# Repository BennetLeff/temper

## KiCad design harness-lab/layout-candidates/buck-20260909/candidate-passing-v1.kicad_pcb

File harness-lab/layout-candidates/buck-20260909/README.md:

# Buck layout candidate — 2026-09-09

`candidate.kicad_pcb` is the verified v4 regrouping of the protected
`buck-dev-a` fixture. Open it directly in KiCad. `compact_candidate.py`
reproduces the placement and routing from `candidate-passing-v1.kicad_pcb`
through KiCad 10.0.4's native API. It resets to that checkpoint on each run;
new track UUIDs mean regenerated bytes need fresh measurements.

The controller sits between the input capacitor above it and the bootstrap
capacitor below it. The feedback divider is on its quiet left side. The
inductor and three output capacitors form a power path to the right. All
nine functional components were placed explicitly; the three terminal
proxies, 50 × 40 mm outline, footprint pad geometry, nets, and rules retain
their frozen identities. No production PCB was edited.

## Verified measurements

| Check | v4 result |
|---|---:|
| Native DRC, including warnings | 0 violations |
| Unconnected items | 0 |
| C9 input pad → U3 VIN copper path | 5.4375 mm |
| C9 ground pad → U3 GND copper path | 11.2875 mm |
| Narrowest power track | 0.6 mm |
| Native reference labels | 12, all 1.0 mm high |
| Electrical/presentation layout judges | pass/pass |
| Atopile-to-PCB circuit integrity | pass |

Board SHA-256:
`03d26c713a13ce1385b49d5582539b27722303341e01de435b9233be5d0e3ee1`.
Protected semantic SHA-256 remains
`e07cf8a38c9066662c222a56ab5304ab0b2659b5b3230561f6c21e3efbc8d2d6`.
`drc.json`, `native-measure.json`, `v4-layout-result.json`, and
`engineering-evidence/` retain the native and Rust results. The full run is
`harness-lab/runs/engineering-audit2-compact-v4/`.

The earlier witness had a 43.7 mm ground route. V1's shortcut achieved
4.489171 mm while retaining the old placement. V4 trades a longer 11.2875 mm
ground route for clearer grouping and a shorter input route. Both meet this
experiment's 20 mm path limit; that limit is a harness proxy, not a TI
electrical specification or proof of acceptable EMI.

## Physical coverage limitation

L2's copied footprint explicitly says **"Stub for Bourns SRP1265A
inductor."** It has two pads, no courtyard, and no 3D body. The native render
therefore shows bare pads, not an inductor envelope. DRC cannot detect body
collisions for this footprint, and the footprint's land pattern is not
manufacturing-qualified.

The Bourns drawing specifies a 13.5 ±0.5 by 12.5 ±0.3 mm body. V4 reserves
the maximum 14.0 × 12.8 mm rectangle around L2, shown on `User.Drawings`;
other components sit outside it. This is a mechanical review aid, not a new
DRC rule or exact 3D model. The terminal footprints are also fixture proxies.
An actual board needs a verified land pattern, courtyard, connectors, and
appropriate copper/thermal design before fabrication. The copied frozen
project continues to ignore `missing_courtyard`; no rule was relaxed here.

The circuit-identity and local layout checks pass. Component derating, model qualification,
16 unresolved mandatory requirements, and powered hardware evidence remain
separate gates. `engineering-evidence/report.json` correctly reports the
complete reference as ineligible.

## Retained attempts

- V1: passing checkpoint, old placement and ground shortcut; its native
  measurements/render are explicitly named `*-v1`.
- V2: 26 DRC violations and 12 opens, retained as `candidate-v2-failed`.
- V3: 23 DRC violations and 2 opens, retained as `candidate-v3-failed`.
- V4 initial check: routing connected and clear; two U3 silkscreen overlaps
  in `v4b-check` were fixed by moving its reference.
- V4 label collection exposed KiCad's required `GetShownText(False)`
  argument. The collector and native visible-label regression now cover it.

The qualitative layout guidance comes from [TI LMR51430 section 9.4](https://www.ti.com/lit/ds/symlink/lmr51430.pdf).
The body envelope comes from the [Bourns SRP1265A drawing](https://bourns.com/docs/product-datasheets/srp1265a.pdf).

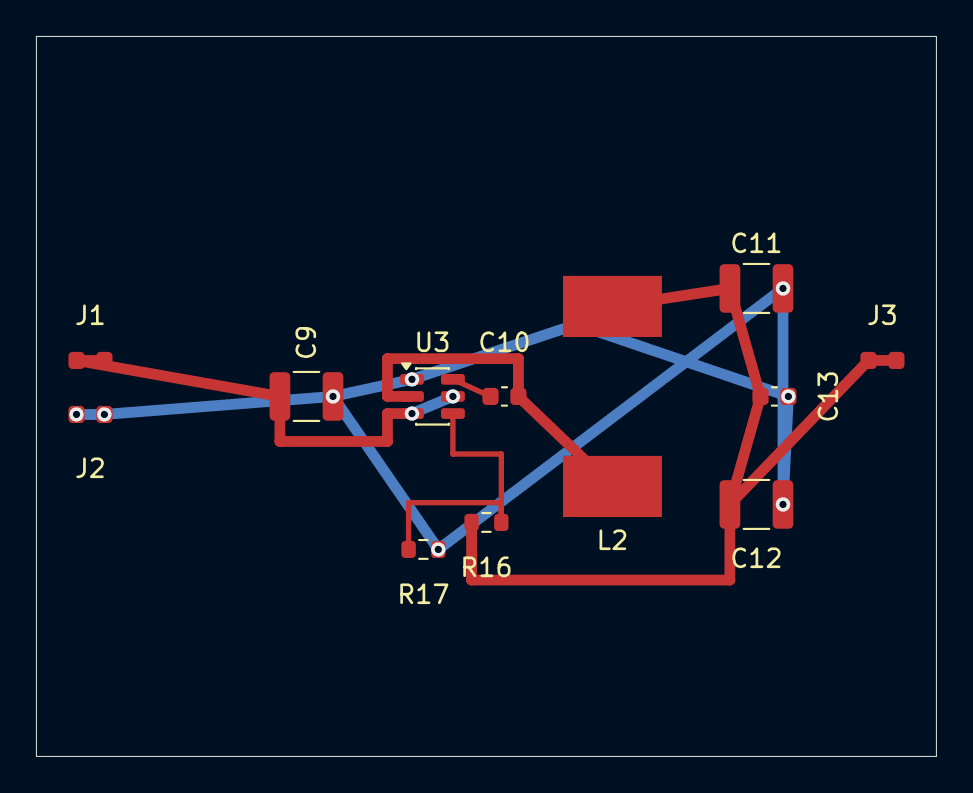
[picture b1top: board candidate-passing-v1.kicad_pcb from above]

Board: 2 copper layers, 50.0 x 40.0 mm, 12 parts (0 on the bottom side), 6 nets.

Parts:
C9: ?; C9
C10: ?; C10
C11: ?; C11
C12: ?; C12
C13: ?; C13
J1: J1
J2: J2
J3: J3
L2: ?; L2
R16: ?; R16
R17: ?; R17
U3: ?; U3

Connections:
+3V3: C11.1, C12.1, C13.1, J3.1, J3.2, L2.2, R16.1
+15V: C9.1, J1.1, J1.2, U3.3, U3.5
boot: C10.1, U3.6
fb: R16.2, R17.1, U3.4
gnd: C9.2, C11.2, C12.2, C13.2, J2.1, J2.2, R17.2, U3.1
sw: C10.2, L2.1, U3.2

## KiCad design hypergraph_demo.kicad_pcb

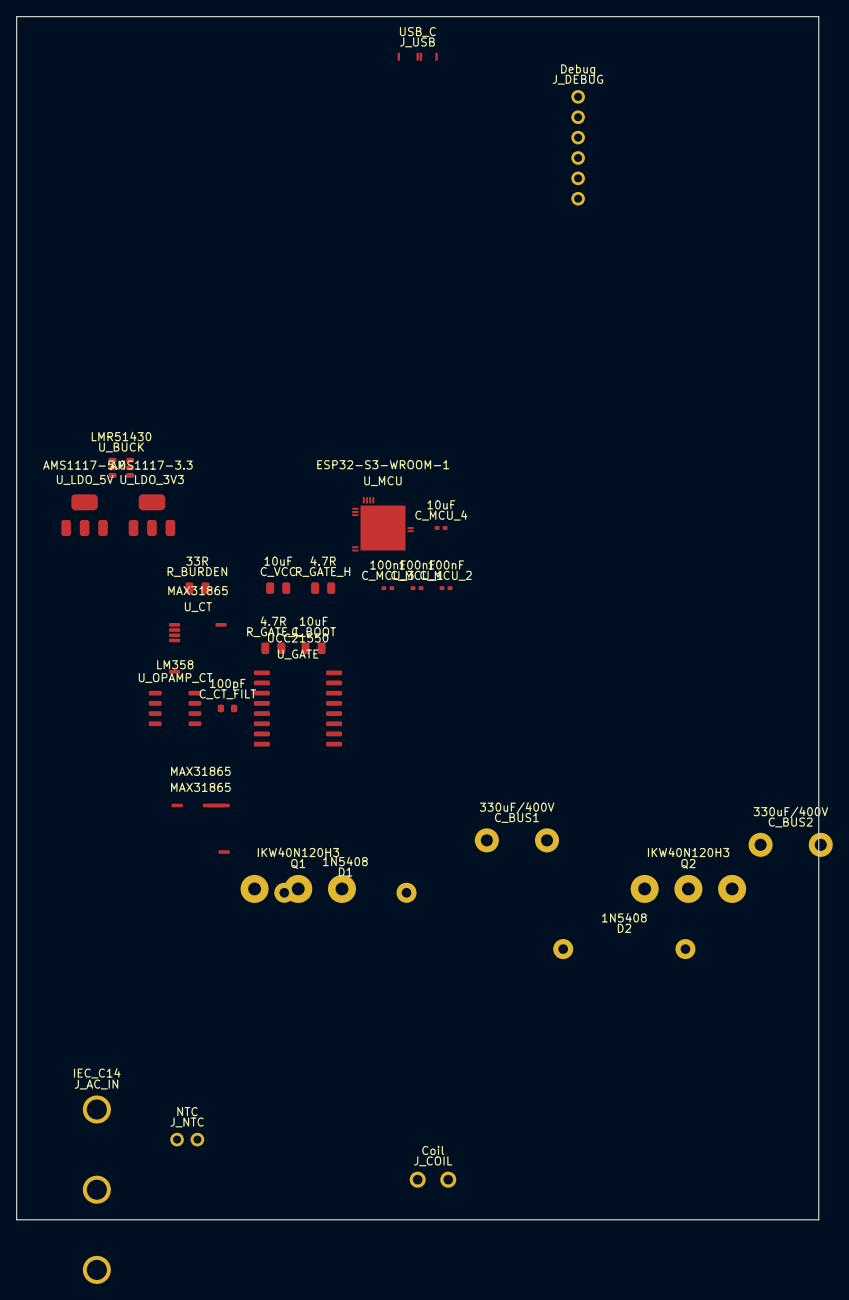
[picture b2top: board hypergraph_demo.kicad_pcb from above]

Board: 4 copper layers, 100.0 x 150.0 mm, 33 parts (0 on the bottom side), 23 nets, no tracks yet.

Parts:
C_BOOT: 10uF; C_0805_2012Metric
C_BUS1, C_BUS2: 330uF/400V; CP_Radial_D18.0mm_P7.50mm
C_CT_FILT: 100pF; C_0603_1608Metric
C_MCU_1, C_MCU_2, C_MCU_3: 100nF; C_0402_1005Metric
C_MCU_4: 10uF; C_0402_1005Metric
C_VCC: 10uF; C_0805_2012Metric
D1, D2: 1N5408; D_DO-201AD_P15.24mm_Horizontal
J_AC_IN: IEC_C14; IEC_C14_Male
J_COIL: Coil; PhoenixContact_MCV_1,5_2-G-3.81_1x02_P3.81mm_Vertical
J_DEBUG: Debug; PinHeader_1x06_P2.54mm_Vertical
J_NTC: NTC; PinHeader_1x02_P2.54mm_Vertical
J_USB: USB_C; USB_C_Receptacle_HRO_TYPE-C-31-M-12
MAX31865: MAX31865; TSSOP-20_4.4x6.5mm_P0.65mm
MH1, MH2, MH3, MH4: MountingHole_3.2mm_M3
Q1, Q2: IKW40N120H3; TO-247-3_Horizontal_TabDown
R_BURDEN: 33R; R_0805_2012Metric
R_GATE_H: 4.7R; R_0805_2012Metric
R_GATE_L: 4.7R; R_0805_2012Metric
U_BUCK: LMR51430; SOT-23-6
U_CT: MAX31865; TSSOP-20_4.4x6.5mm_P0.65mm
U_GATE: UCC21550; SOIC-16W_7.5x10.3mm_P1.27mm
U_LDO_3V3: AMS1117-3.3; SOT-223-3_TabPin2
U_LDO_5V: AMS1117-5.0; SOT-223-3_TabPin2
U_MCU: ESP32-S3-WROOM-1; QFN-56-1EP_7x7mm_P0.4mm_EP5.6x5.6mm
U_OPAMP_CT: LM358; SOIC-8_3.9x4.9mm_P1.27mm

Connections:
+3V3: C_MCU_1.1, C_MCU_2.1, C_MCU_3.1, C_MCU_4.1, J_DEBUG.2, MAX31865.20, U_CT.20, U_LDO_3V3.2, U_LDO_3V3.4, U_MCU.1
+5V: U_BUCK.2, U_BUCK.4, U_LDO_3V3.3, U_LDO_5V.2, U_LDO_5V.4, U_OPAMP_CT.7, U_OPAMP_CT.8
+15V: C_VCC.1, U_BUCK.3, U_GATE.1, U_GATE.11, U_LDO_5V.3
AC_L: D1.1, J_AC_IN.1
AC_N: D2.2, J_AC_IN.2
CGND: C_VCC.2, U_GATE.5, U_GATE.6, U_GATE.7, U_GATE.8
DC_BUS+: C_BUS1.1, C_BUS2.1, D1.2, Q1.3
GATE_H: Q1.1, R_GATE_H.1, R_GATE_H.2, U_GATE.15
GATE_L: Q2.1, R_GATE_L.1, R_GATE_L.2, U_GATE.10
GND: C_CT_FILT.2, C_MCU_1.2, C_MCU_2.2, C_MCU_3.2, C_MCU_4.2, J_AC_IN.3, J_COIL.2, J_DEBUG.1, J_NTC.2, J_USB.A1, J_USB.A12, MAX31865.10, R_BURDEN.2, U_BUCK.1, U_BUCK.5, U_BUCK.6, U_CT.10, U_LDO_3V3.1, U_LDO_5V.1, U_MCU.2, U_MCU.57, U_OPAMP_CT.4
I_SENSE: C_CT_FILT.1, R_BURDEN.1, U_MCU.15, U_OPAMP_CT.1, U_OPAMP_CT.2, U_OPAMP_CT.3, U_OPAMP_CT.5, U_OPAMP_CT.6
PGND: C_BUS1.2, C_BUS2.2, Q2.2, U_GATE.12, U_GATE.13
PWM_H: U_GATE.2, U_MCU.13
PWM_L: U_GATE.3, U_MCU.14
SPI_CLK: MAX31865.1, U_CT.1, U_MCU.20
SPI_CS_TEMP: U_CT.4, U_MCU.23
SPI_MISO: MAX31865.3, U_CT.3, U_MCU.22
SPI_MOSI: MAX31865.2, U_CT.2, U_MCU.21
SW_NODE: C_BOOT.2, J_COIL.1, Q1.2, Q2.3, U_GATE.9, U_GATE.16
TEMP_SENSE: J_NTC.1, MAX31865.4
USB_D+: J_USB.A6, U_MCU.40
USB_D-: J_USB.B6, U_MCU.41
VCC_BOOT: C_BOOT.1, U_GATE.14
